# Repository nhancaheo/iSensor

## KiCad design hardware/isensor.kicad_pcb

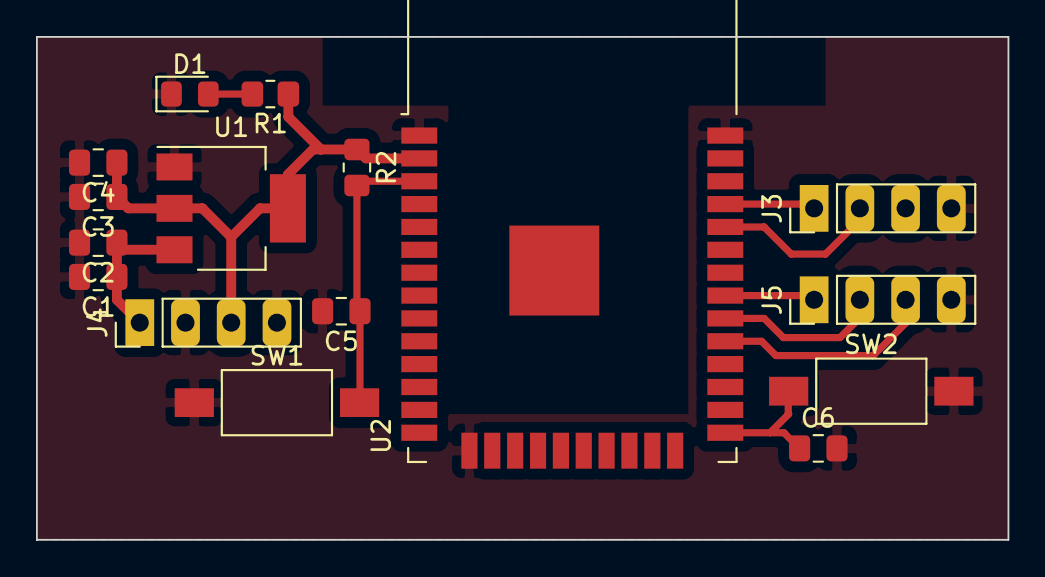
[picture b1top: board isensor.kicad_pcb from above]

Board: 2 copper layers, 54.0 x 27.9 mm, 16 parts (0 on the bottom side), 11 nets.

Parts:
C1, C3: 100n; C_0805_2012Metric_Pad1.18x1.45mm_HandSolder
C2: 10uF; C_0805_2012Metric_Pad1.18x1.45mm_HandSolder
C4: 100uF; C_0805_2012Metric_Pad1.18x1.45mm_HandSolder
C5, C6: 100nF; C_0805_2012Metric_Pad1.18x1.45mm_HandSolder
D1: LED_Small; LED_0805_2012Metric_Pad1.15x1.40mm_HandSolder
J3, J4, J5: Conn_01x04_Female; PinHeader_1x04_P2.54mm_Vertical_Nhan
R1: 220; R_0805_2012Metric_Pad1.20x1.40mm_HandSolder
R2: 10k; R_0805_2012Metric_Pad1.20x1.40mm_HandSolder
SW1, SW2: SW_Push; SW_SPST_FSMSM
U1: AMS1117-3.3; SOT-223-3_TabPin2
U2: ESP32-WROOM-32D; ESP32-WROOM-32

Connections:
/3.3V: C3.1, C4.1, J3.3, J4.3, R1.1, R2.1, U1.2, U2.2
/IO5: J5.3, U2.29
/IO18: J5.2, U2.30
/IO19: J5.1, U2.31
/UART_RX: J3.2, U2.34
/UART_TX: J3.1, U2.35
/VIN: C1.1, C2.1, J4.1, U1.3
GND: C1.2, C2.2, C3.2, C4.2, C5.2, C6.2, D1.1, J3.4, J4.2, J4.4, J5.4, SW1.1, SW2.2, U1.1, U2.1, U2.15, U2.38, U2.39
unnamed: C5.1, R2.2, SW1.2, U2.3
unnamed: C6.1, SW2.1, U2.25
unnamed: D1.2, R1.2

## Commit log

2021-06-14 Added PCB files.
2021-06-14 Added .gitignore file.
2021-06-14 Added software files.
